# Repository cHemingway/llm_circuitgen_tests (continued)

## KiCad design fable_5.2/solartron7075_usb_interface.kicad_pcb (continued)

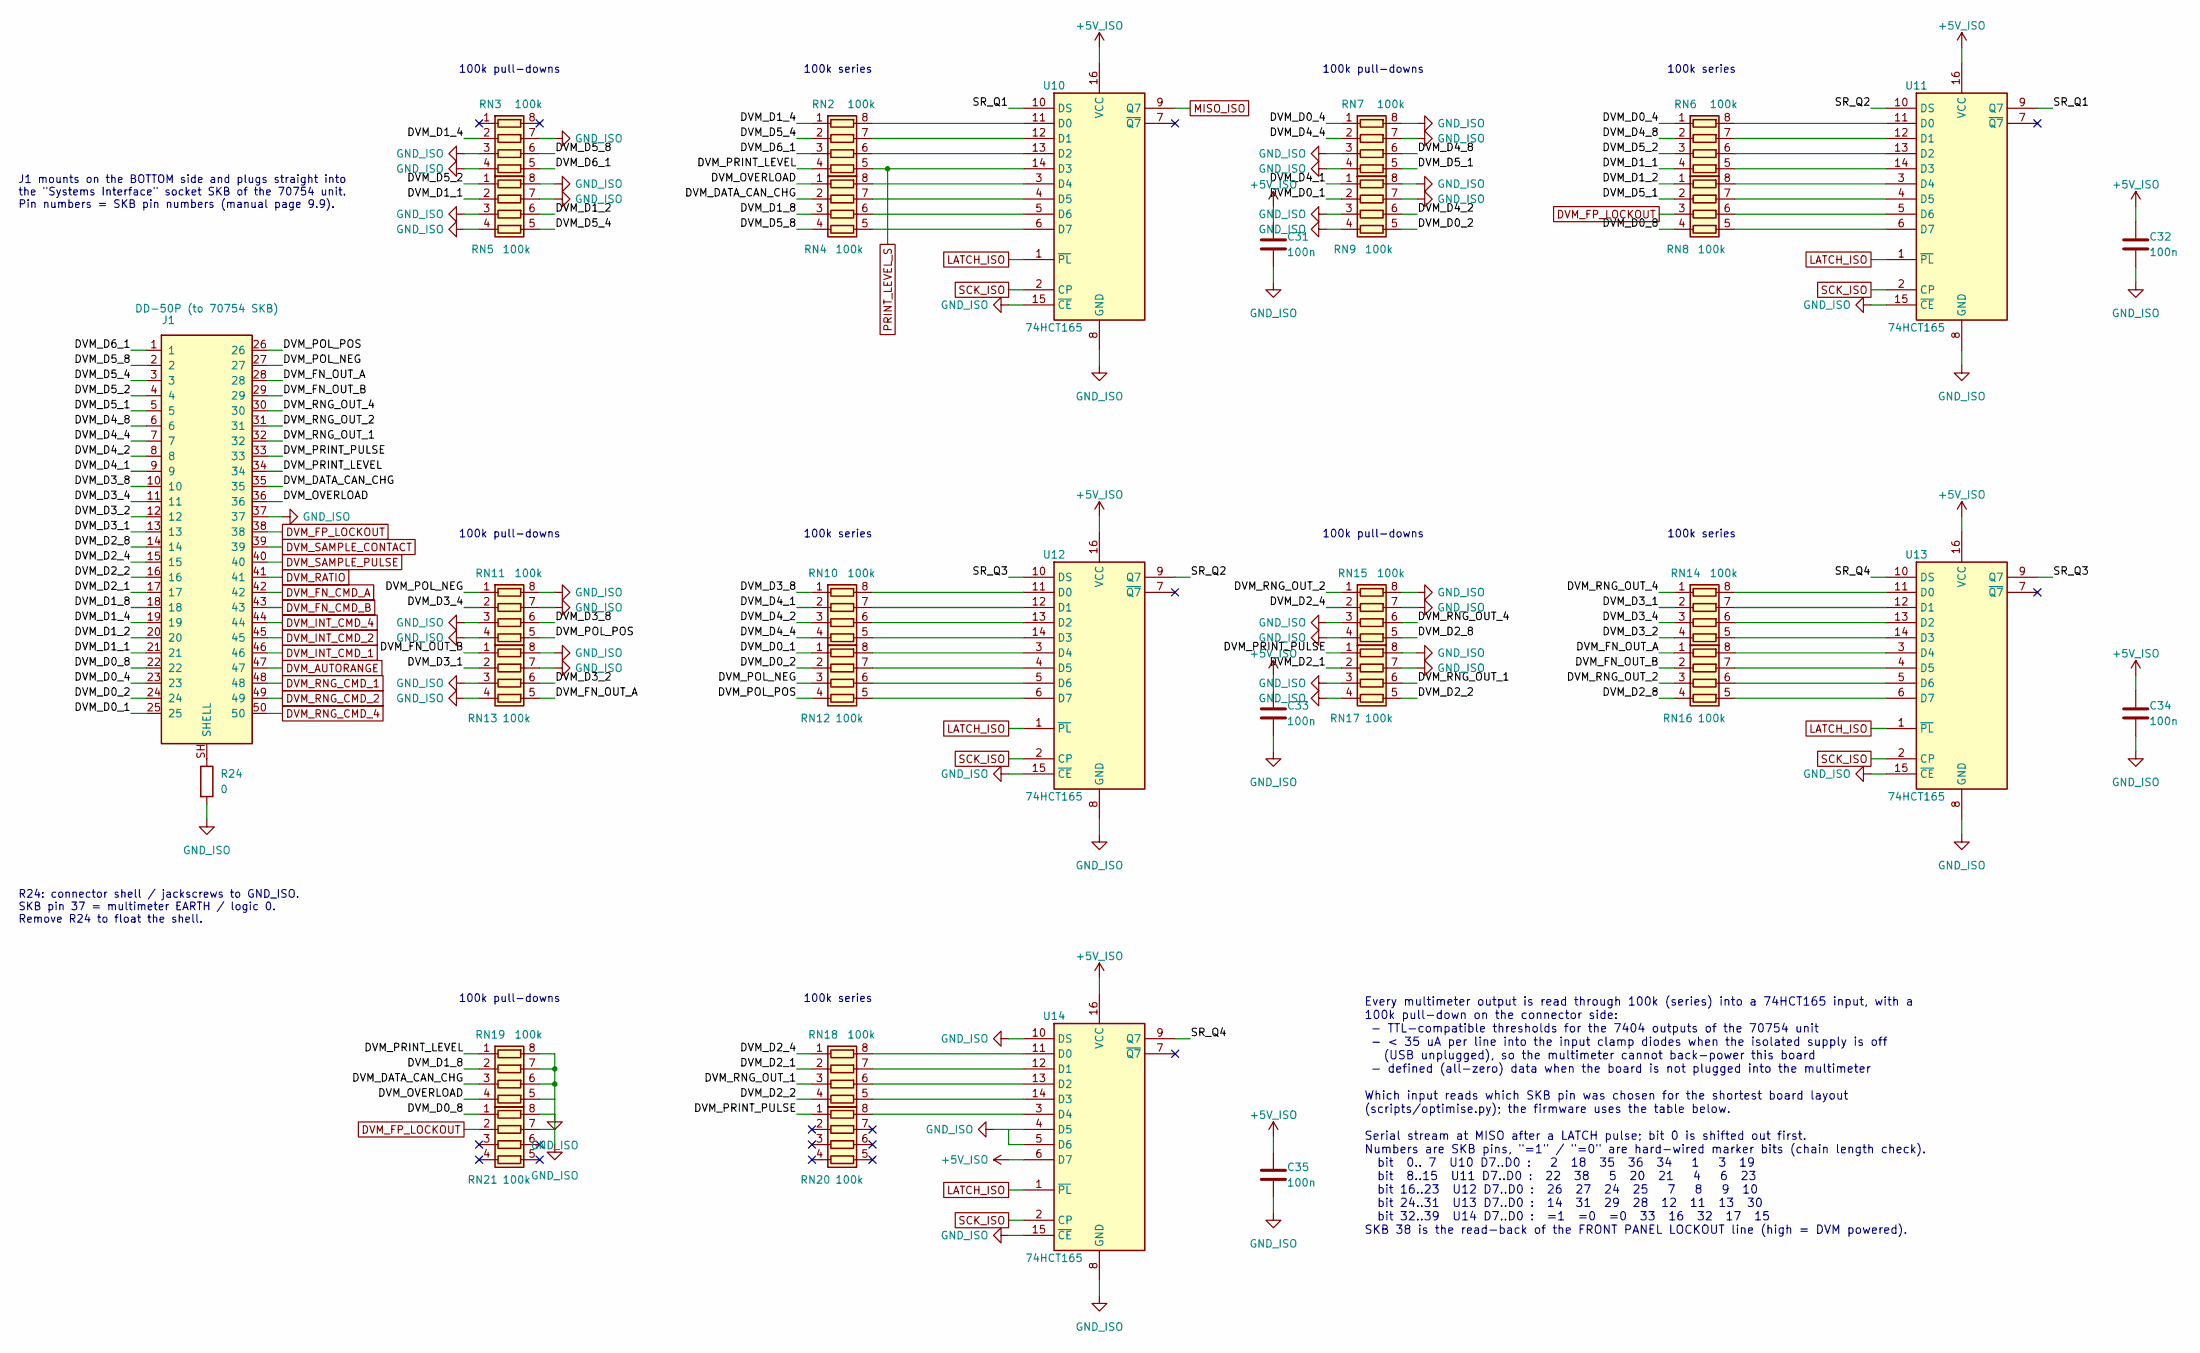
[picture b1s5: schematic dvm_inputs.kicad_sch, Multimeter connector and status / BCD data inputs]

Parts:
C31, C32, C33, C34, C35: 100n; C_0603_1608Metric; MPN CC0603KRX7R9BB104; LCSC C14663
J1: DD-50P (to 70754 SKB); DSUB-50_Pins_Vertical_P2.76x2.84mm_MountingHoles; MPN DD50P364TXLF; LCSC C5402574
R24: 0; R_0603_1608Metric; MPN 0603WAF0000T5E; LCSC C21189
RN2, RN3, RN4, RN5, RN6, RN7, RN8, RN9, RN10, RN11, RN12, RN13, RN14, RN15, RN16, RN17, RN18, RN19, RN20, RN21: 100k; R_Array_Convex_4x0603; MPN YC164-JR-07100KL; LCSC C192933
U10, U11, U12, U13, U14: 74HCT165; SOIC-16_3.9x9.9mm_P1.27mm; MPN 74HCT165D,653; LCSC C456131

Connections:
+5V_ISO: C31.1, C32.1, C33.1, C34.1, C35.1, U10.16 (VCC), U11.16 (VCC), U12.16 (VCC), U13.16 (VCC), U14.6 (D7), U14.16 (VCC); also elsewhere on the board
/DVM_INPUTS/DVM_D0_1: J1.25, RN9.2 (R2.1), RN12.1 (R1.1)
/DVM_INPUTS/DVM_D0_2: J1.24, RN9.5 (R4.2), RN12.2 (R2.1)
/DVM_INPUTS/DVM_D0_4: J1.23, RN6.1 (R1.1), RN7.1 (R1.1)
/DVM_INPUTS/DVM_D0_8: J1.22, RN8.4 (R4.1), RN21.1 (R1.1)
/DVM_INPUTS/DVM_D1_1: J1.21, RN5.2 (R2.1), RN6.4 (R4.1)
/DVM_INPUTS/DVM_D1_2: J1.20, RN5.6 (R3.2), RN8.1 (R1.1)
/DVM_INPUTS/DVM_D1_4: J1.19, RN2.1 (R1.1), RN3.2 (R2.1)
/DVM_INPUTS/DVM_D1_8: J1.18, RN4.3 (R3.1), RN19.2 (R2.1)
/DVM_INPUTS/DVM_D2_1: J1.17, RN17.2 (R2.1), RN18.2 (R2.1)
/DVM_INPUTS/DVM_D2_2: J1.16, RN17.5 (R4.2), RN18.4 (R4.1)
/DVM_INPUTS/DVM_D2_4: J1.15, RN15.2 (R2.1), RN18.1 (R1.1)
/DVM_INPUTS/DVM_D2_8: J1.14, RN15.5 (R4.2), RN16.4 (R4.1)
/DVM_INPUTS/DVM_D3_1: J1.13, RN13.2 (R2.1), RN14.2 (R2.1)
/DVM_INPUTS/DVM_D3_2: J1.12, RN13.6 (R3.2), RN14.4 (R4.1)
/DVM_INPUTS/DVM_D3_4: J1.11, RN11.2 (R2.1), RN14.3 (R3.1)
/DVM_INPUTS/DVM_D3_8: J1.10, RN10.1 (R1.1), RN11.6 (R3.2)
/DVM_INPUTS/DVM_D4_1: J1.9, RN9.1 (R1.1), RN10.2 (R2.1)
/DVM_INPUTS/DVM_D4_2: J1.8, RN9.6 (R3.2), RN10.3 (R3.1)
/DVM_INPUTS/DVM_D4_4: J1.7, RN7.2 (R2.1), RN10.4 (R4.1)
/DVM_INPUTS/DVM_D4_8: J1.6, RN6.2 (R2.1), RN7.6 (R3.2)
/DVM_INPUTS/DVM_D5_1: J1.5, RN7.5 (R4.2), RN8.2 (R2.1)
/DVM_INPUTS/DVM_D5_2: J1.4, RN5.1 (R1.1), RN6.3 (R3.1)
/DVM_INPUTS/DVM_D5_4: J1.3, RN2.2 (R2.1), RN5.5 (R4.2)
/DVM_INPUTS/DVM_D5_8: J1.2, RN3.6 (R3.2), RN4.4 (R4.1)
/DVM_INPUTS/DVM_D6_1: J1.1, RN2.3 (R3.1), RN3.5 (R4.2)
/DVM_INPUTS/DVM_DATA_CAN_CHG: J1.35, RN4.2 (R2.1), RN19.3 (R3.1)
/DVM_INPUTS/DVM_FN_OUT_A: J1.28, RN13.5 (R4.2), RN16.1 (R1.1)
/DVM_INPUTS/DVM_FN_OUT_B: J1.29, RN13.1 (R1.1), RN16.2 (R2.1)
/DVM_INPUTS/DVM_OVERLOAD: J1.36, RN4.1 (R1.1), RN19.4 (R4.1)
/DVM_INPUTS/DVM_POL_NEG: J1.27, RN11.1 (R1.1), RN12.3 (R3.1)
/DVM_INPUTS/DVM_POL_POS: J1.26, RN11.5 (R4.2), RN12.4 (R4.1)
/DVM_INPUTS/DVM_PRINT_LEVEL: J1.34, RN2.4 (R4.1), RN19.1 (R1.1)
/DVM_INPUTS/DVM_PRINT_PULSE: J1.33, RN17.1 (R1.1), RN20.1 (R1.1)
/DVM_INPUTS/DVM_RNG_OUT_1: J1.32, RN17.6 (R3.2), RN18.3 (R3.1)
/DVM_INPUTS/DVM_RNG_OUT_2: J1.31, RN15.1 (R1.1), RN16.3 (R3.1)
/DVM_INPUTS/DVM_RNG_OUT_4: J1.30, RN14.1 (R1.1), RN15.6 (R3.2)
/DVM_INPUTS/SR_Q1: U10.10 (DS), U11.9 (Q7)
/DVM_INPUTS/SR_Q2: U11.10 (DS), U12.9 (Q7)
/DVM_INPUTS/SR_Q3: U12.10 (DS), U13.9 (Q7)
/DVM_INPUTS/SR_Q4: U13.10 (DS), U14.9 (Q7)
DVM_AUTORANGE: J1.47; also elsewhere on the board
DVM_FN_CMD_A: J1.42; also elsewhere on the board
DVM_FN_CMD_B: J1.43; also elsewhere on the board
DVM_FP_LOCKOUT: J1.38, RN8.3 (R3.1), RN21.2 (R2.1); also elsewhere on the board
DVM_INT_CMD_1: J1.46; also elsewhere on the board
DVM_INT_CMD_2: J1.45; also elsewhere on the board
DVM_INT_CMD_4: J1.44; also elsewhere on the board
DVM_RATIO: J1.41; also elsewhere on the board
DVM_RNG_CMD_1: J1.48; also elsewhere on the board
DVM_RNG_CMD_2: J1.49; also elsewhere on the board
DVM_RNG_CMD_4: J1.50; also elsewhere on the board
DVM_SAMPLE_CONTACT: J1.39; also elsewhere on the board
DVM_SAMPLE_PULSE: J1.40; also elsewhere on the board
GND_ISO: C31.2, C32.2, C33.2, C34.2, C35.2, J1.37, R24.2, RN3.3 (R3.1), RN3.4 (R4.1), RN3.7 (R2.2), RN5.3 (R3.1), RN5.4 (R4.1), RN5.7 (R2.2), RN5.8 (R1.2), RN7.3 (R3.1), RN7.4 (R4.1), RN7.7 (R2.2), RN7.8 (R1.2), RN9.3 (R3.1), RN9.4 (R4.1), RN9.7 (R2.2), RN9.8 (R1.2), RN11.3 (R3.1), RN11.4 (R4.1), RN11.7 (R2.2), RN11.8 (R1.2), RN13.3 (R3.1), RN13.4 (R4.1), RN13.7 (R2.2), RN13.8 (R1.2), RN15.3 (R3.1), RN15.4 (R4.1), RN15.7 (R2.2), RN15.8 (R1.2), RN17.3 (R3.1), RN17.4 (R4.1), RN17.7 (R2.2), RN17.8 (R1.2), RN19.5 (R4.2), RN19.6 (R3.2), RN19.7 (R2.2), RN19.8 (R1.2), RN21.7 (R2.2), RN21.8 (R1.2), U10.8 (GND), U10.15 (~CE), U11.8 (GND), U11.15 (~CE), U12.8 (GND), U12.15 (~CE), U13.8 (GND), U13.15 (~CE), U14.4 (D5), U14.5 (D6), U14.8 (GND), U14.10 (DS), U14.15 (~CE); also elsewhere on the board
LATCH_ISO: U10.1 (~PL), U11.1 (~PL), U12.1 (~PL), U13.1 (~PL), U14.1 (~PL); also elsewhere on the board
MISO_ISO: U10.9 (Q7); also elsewhere on the board
unnamed: J1.SH (SHELL), R24.1
unnamed: RN2.8 (R1.2), U10.11 (D0)
unnamed: RN2.7 (R2.2), U10.12 (D1)
unnamed: RN2.6 (R3.2), U10.13 (D2)
unnamed: RN4.8 (R1.2), U10.3 (D4)
unnamed: RN4.7 (R2.2), U10.4 (D5)
unnamed: RN4.6 (R3.2), U10.5 (D6)
unnamed: RN4.5 (R4.2), U10.6 (D7)
unnamed: RN6.8 (R1.2), U11.11 (D0)
unnamed: RN6.7 (R2.2), U11.12 (D1)
unnamed: RN6.6 (R3.2), U11.13 (D2)
unnamed: RN6.5 (R4.2), U11.14 (D3)
unnamed: RN8.8 (R1.2), U11.3 (D4)
unnamed: RN8.7 (R2.2), U11.4 (D5)
unnamed: RN8.6 (R3.2), U11.5 (D6)
unnamed: RN8.5 (R4.2), U11.6 (D7)
unnamed: RN10.8 (R1.2), U12.11 (D0)
unnamed: RN10.7 (R2.2), U12.12 (D1)
unnamed: RN10.6 (R3.2), U12.13 (D2)
unnamed: RN10.5 (R4.2), U12.14 (D3)
unnamed: RN12.8 (R1.2), U12.3 (D4)
unnamed: RN12.7 (R2.2), U12.4 (D5)
unnamed: RN12.6 (R3.2), U12.5 (D6)
unnamed: RN12.5 (R4.2), U12.6 (D7)
unnamed: RN14.8 (R1.2), U13.11 (D0)
unnamed: RN14.7 (R2.2), U13.12 (D1)
unnamed: RN14.6 (R3.2), U13.13 (D2)
unnamed: RN14.5 (R4.2), U13.14 (D3)
unnamed: RN16.8 (R1.2), U13.3 (D4)
unnamed: RN16.7 (R2.2), U13.4 (D5)
unnamed: RN16.6 (R3.2), U13.5 (D6)
unnamed: RN16.5 (R4.2), U13.6 (D7)
unnamed: RN18.8 (R1.2), U14.11 (D0)
unnamed: RN18.7 (R2.2), U14.12 (D1)
unnamed: RN18.6 (R3.2), U14.13 (D2)
unnamed: RN18.5 (R4.2), U14.14 (D3)
unnamed: RN20.8 (R1.2), U14.3 (D4)
PRINT_LEVEL_S: RN2.5 (R4.2), U10.14 (D3); also elsewhere on the board
SCK_ISO: U10.2 (CP), U11.2 (CP), U12.2 (CP), U13.2 (CP), U14.2 (CP); also elsewhere on the board

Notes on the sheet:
R24: connector shell / jackscrews to GND_ISO. SKB pin 37 = multimeter EARTH / logic 0. Remove R24 to float the shell.
J1 mounts on the BOTTOM side and plugs straight into the "Systems Interface" socket SKB of the 70754 unit. Pin numbers = SKB pin numbers (manual page 9.9).
100k pull-downs
100k series
Every multimeter output is read through 100k (series) into a 74HCT165 input, with a 100k pull-down on the connector side: - TTL-compatible thresholds for the 7404 outputs of the 70754 unit - < 35 uA per line into the input clamp diodes when the isolated supply is off (USB unplugged), so the multime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

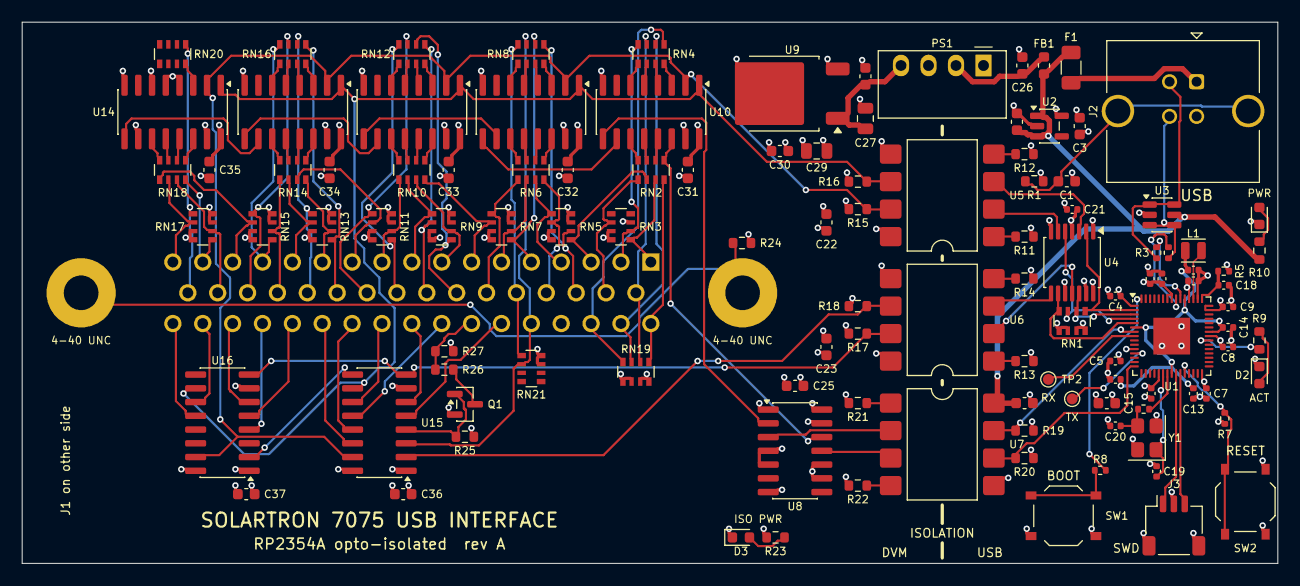
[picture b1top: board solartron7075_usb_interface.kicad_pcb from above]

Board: 4 copper layers, 116.0 x 50.0 mm, 116 parts (1 on the bottom side), 147 nets.

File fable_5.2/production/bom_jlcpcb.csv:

Comment,Designator,Footprint,LCSC Part #,MPN,Manufacturer,Qty,Description
4.7n,C1,C_0603_1608Metric,C106218,CC0603KRX7R9BB472,YAGEO,1,4.7nF 50V X7R MLCC 0603
4.7u,"C2,C26",C_0603_1608Metric,C19666,CL10A475KO8NNNC,Samsung,2,4.7uF 16V X5R MLCC 0603
10u,"C3,C15",C_0603_1608Metric,C19702,CL10A106KP8NNNC,Samsung,2,10uF 10V X5R MLCC 0603
100n,"C4,C5,C6,C7,C8,C9,C10,C11,C12,C13,C14,C21",C_0402_1005Metric,C1525,CL05B104KO5NNNC,Samsung,12,100nF 16V X7R MLCC 0402
4.7u,"C16,C17,C18",C_0402_1005Metric,C23733,CL05A475MP5NRNC,Samsung,3,4.7uF 10V X5R MLCC 0402
15p,"C19,C20",C_0402_1005Metric,C1548,0402CG150J500NT,FH,2,15pF 50V C0G MLCC 0402
100n,"C22,C23,C24,C25,C28,C30,C31,C32,C33,C34,C35,C36,C37",C_0603_1608Metric,C14663,CC0603KRX7R9BB104,YAGEO,13,100nF 50V X7R MLCC 0603
10u,"C27,C29",C_0805_2012Metric,C15850,CL21A106KAYNNNE,Samsung,2,10uF 25V X5R MLCC 0805
GREEN,"D1,D3",LED_0603_1608Metric,C12624,KT-0603G,Hubei KENTO,2,0603 green LED
RED,D2,LED_0603_1608Metric,C2286,KT-0603R,Hubei KENTO,1,0603 red LED
500mA,F1,Fuse_1206_3216Metric,C70075,nSMD050-16V,TECHFUSE,1,"PTC resettable fuse 0.5 A hold / 1 A trip, 16 V, 1206"
120R@100MHz,FB1,L_0603_1608Metric,C14709,BLM18PG121SN1D,Murata,1,"Ferrite bead 120 ohm @ 100 MHz, 2 A, 0603"
DD-50P (to 70754 SKB),J1,DSUB-50_Pins_Vertical_P2.76x2.84mm_MountingHoles,C5402574,DD50P364TXLF,Amphenol ICC,1,"50-way 3-row standard-density D-sub plug (DD-50P), straight PCB pins, plain 3.1 mm flange holes"
USB-B vertical,J2,USB_B_TE_5787834_Vertical,C592900,5787834-1,TE Connectivity,1,"USB 2.0 type B receptacle, vertical, THT"
SWD,J3,JST_SH_SM03B-SRSS-TB_1x03-1MP_P1.00mm_Horizontal,C160403,SM03B-SRSS-TB(LF)(SN),JST,1,"Raspberry Pi 3-pin debug connector (JST-SH): 1 SWCLK, 2 GND, 3 SWDIO"
3.3uH,L1,L_Abracon_AOTA-B201610S,C42411119,AOTA-B201610S3R3-101-T,Abracon,1,"3.3 uH 2.1 A polarised power inductor 2016 (pad 1 / dot = +1V1 output side, as in the RP2350 reference layout)"
B0509S-1WR3,PS1,Converter_DCDC_Mornsun_B05xxS-1WR3_SIP4_THT,C5369463,B0509S-1WR3,YLPTEC (Mornsun B0509S-1WR3 compatible),1,"Isolated 1 W DC-DC converter 5 V -> 9 V / 111 mA, 1.5 kV, SIP-4 (Murata MEE1S0509SC pin compatible)"
AO3401A,Q1,SOT-23,C15127,AO3401A,Alpha & Omega,1,P-channel MOSFET -30 V -4 A SOT-23
1M,R1,R_0603_1608Metric,C22935,0603WAF1004T5E,UNI-ROYAL,1,Resistor
27,"R2,R3",R_0402_1005Metric,C25100,0402WGF270JTCE,UNI-ROYAL,2,Resistor
33,R5,R_0402_1005Metric,C25105,0402WGF330JTCE,UNI-ROYAL,1,Resistor
1k,"R6,R8",R_0402_1005Metric,C11702,0402WGF1001TCE,UNI-ROYAL,2,Resistor
10k,R7,R_0402_1005Metric,C25744,0402WGF1002TCE,UNI-ROYAL,1,Resistor
1k,"R9,R10,R17,R19,R20,R23",R_0603_1608Metric,C21190,0603WAF1001T5E,UNI-ROYAL,6,Resistor
180,"R11,R12,R13,R14",R_0603_1608Metric,C22828,0603WAF1800T5E,UNI-ROYAL,4,Resistor
470,"R15,R16,R18",R_0603_1608Metric,C23179,0603WAF4700T5E,UNI-ROYAL,3,Resistor
390,"R21,R22",R_0603_1608Metric,C23151,0603WAF3900T5E,UNI-ROYAL,2,Resistor
0,R24,R_0603_1608Metric,C21189,0603WAF0000T5E,UNI-ROYAL,1,Resistor
10k,R25,R_0603_1608Metric,C25804,0603WAF1002T5E,UNI-ROYAL,1,Resistor
100,R26,R_0603_1608Metric,C22775,0603WAF1000T5E,UNI-ROYAL,1,Resistor
4.7k,R27,R_0603_1608Metric,C23162,0603WAF4701T5E,UNI-ROYAL,1,Resistor
10k,RN1,R_Array_Convex_4x0603,C29718,4D03WGJ0103T5E,UNI-ROYAL,1,4x 10k 5% resistor array 0603x4
100k,"RN2,RN3,RN4,RN5,RN6,RN7,RN8,RN9,RN10,RN11,RN12,RN13,RN14,RN15,RN16,RN17,RN18,RN19,RN20,RN21",R_Array_Convex_4x0603,C192933,YC164-JR-07100KL,YAGEO,20,4x 100k 5% resistor array 0603x4
BOOTSEL,SW1,SW_Push_1P1T_XKB_TS-1187A,C318884,TS-1187A-B-A-B,XKB Connection,1,Tactile switch 5.1x5.1 mm SMD
RESET,SW2,SW_Push_1P1T_XKB_TS-1187A,C318884,TS-1187A-B-A-B,XKB Connection,1,Tactile switch 5.1x5.1 mm SMD
RP2354A,U1,QFN-60-1EP_7x7mm_P0.4mm_EP3.4x3.4mm,C41378174,RP2354A,Raspberry Pi,1,"A microcontroller by Raspberry Pi, dual CPU architecture (ARM Cortex-M33 / RISC-V Hazard3), 150MHz, 2MB flash, 520KB SRAM, 12 PIO state machines, VQFN-60"
AP2112K-3.3,U2,SOT-23-5,C51118,AP2112K-3.3TRG1,Diodes Inc.,1,"600mA low dropout linear regulator, with enable pin, 3.8V-6V input voltage range, 3.3V fixed positive output, SOT-23-5"
USBLC6-2SC6,U3,SOT-23-6,C7519,USBLC6-2SC6,STMicroelectronics,1,"Very low capacitance ESD protection diode, 2 data-line, SOT-23-6"
74LVC125,U4,TSSOP-14_4.4x5mm_P0.65mm,C7813,SN74LVC125APWR,Texas Instruments,1,Quad buffer 3-State outputs
HCPL-2631,"U5,U6,U7",SMDIP-8_W9.53mm,C188742,HCPL-2631-500E,Broadcom,3,"Dual 10 MBd logic-gate optocoupler, open-collector outputs, gull-wing SMD-8"
74AHCT125,U8,SOIC-14_3.9x8.7mm_P1.27mm,C155176,SN74AHCT125DR,Texas Instruments,1,Quadruple Bus Buffer Gates With 3-State Outputs
L78M05,U9,TO-252-2,C58069,L78M05ABDT-TR,STMicroelectronics,1,"5 V 500 mA linear regulator, DPAK"
74HCT165,"U10,U11,U12,U13,U14",SOIC-16_3.9x9.9mm_P1.27mm,C456131,"74HCT165D,653",Nexperia,5,"8-bit parallel-in serial-out shift register, TTL-compatible inputs, SOIC-16"
TPIC6C595,"U15,U16",SOIC-16_3.9x9.9mm_P1.27mm,C350572,TPIC6C595DR,Texas Instruments,2,"Power logic 8-bit shift register, open-drain DMOS outputs 33 V / 100 mA, SOIC-16"
12MHz,Y1,Crystal_SMD_3225-4Pin_3.2x2.5mm,C20625731,ABM8-272-T3,Abracon,1,"12 MHz crystal, CL = 10 pF, 3225"
